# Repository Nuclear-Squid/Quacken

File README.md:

# Quacken

Libre, ergonomic, *polymorphic*: a single PCB for many possible layouts.

[3×6, 3×5, hummingbird, and everything in between](https://html-preview.github.io/?url=https%3A%2F%2Fgithub.com%2FNuclear-Squid%2FQuacken%2Fblob%2Fmain%2Findex.html).

## Roadmap

- [x] **Quacken Zero**: unibody
  - [x] first batch with a Pro Micro slot, to experiment geometry and design choices
  - [ ] next batches with an onboard nRF52840 (Bluetooth LE) and the updated geometry

- [x] **Quacken Flex**: unibody by default, splittable by choice
  - [x] onboard RP2040 (left) and I/O expander (right)
  - [x] splittable in two (I²C communication over a TRRS cable)
  - [x] splittable outer columns
  - [ ] hotswap sockets
  - [ ] optional Circle Trackpad
  - [x] optional rotary encoders

- [ ] **Marie-Quackenette**: split and wireless variant of the Quacken Flex.

## To flash the Quacken

You just need to push the little switch near the MCU, with the lightning sign, while you plug the USB cable in. Your Quacken will be detected as a storage device.
You may copy your beloved config file on this device through your file manager.
The Quacken will read the new file and reboot in normal mode, with your new config applied.

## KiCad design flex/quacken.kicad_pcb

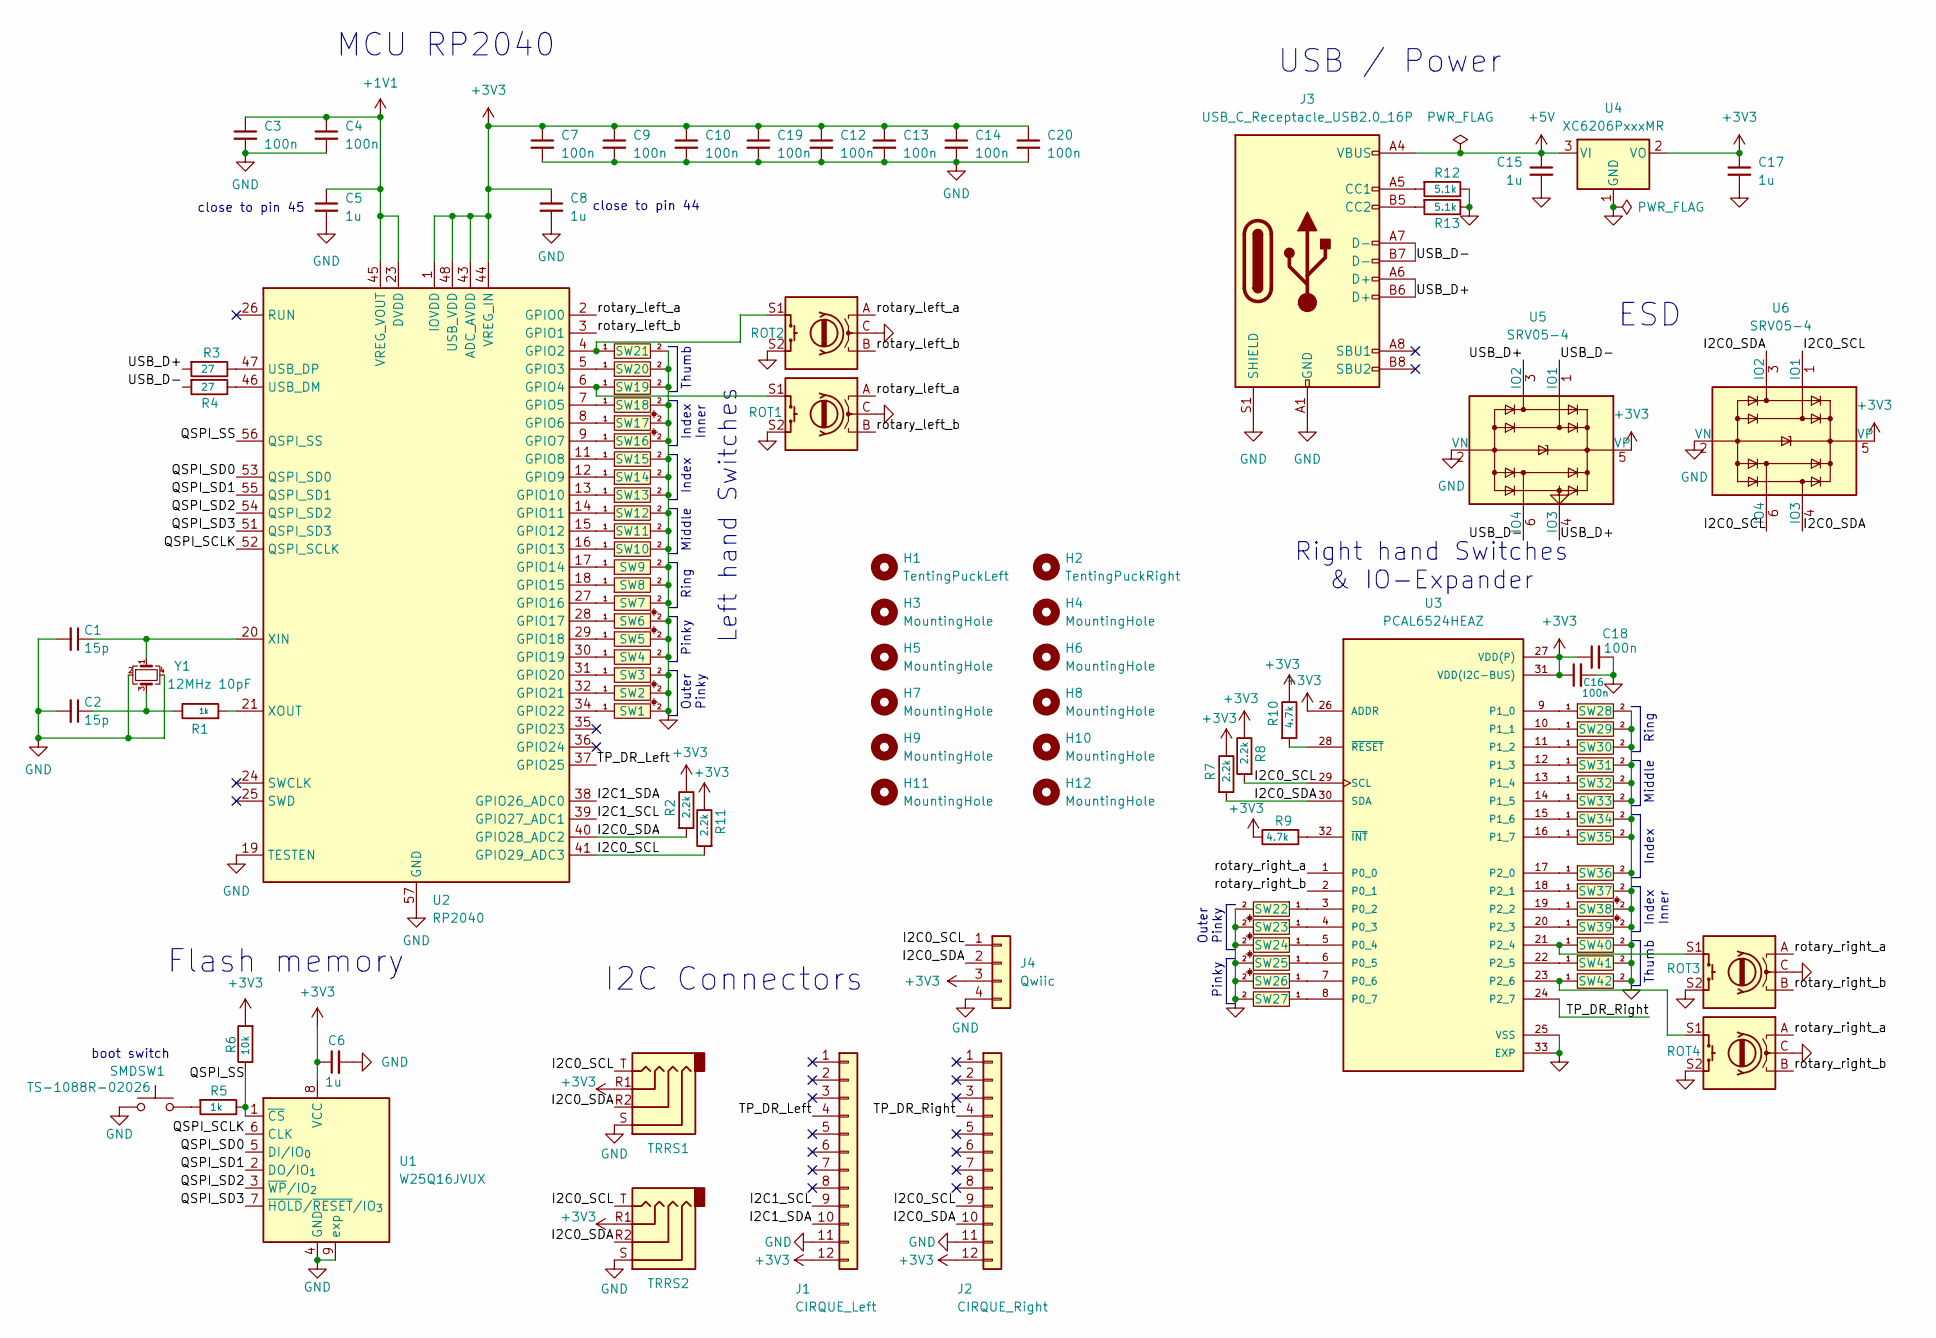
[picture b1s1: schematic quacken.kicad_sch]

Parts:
C1, C2: 15p; C_0402_1005Metric
C3, C4, C7, C9, C10, C12, C13, C14, C16, C18, C19, C20: 100n; C_0402_1005Metric
C5, C6, C8, C15, C17: 1u; C_0402_1005Metric
H1: TentingPuckLeft; TentingPuck
H2: TentingPuckRight; TentingPuck
H3, H4, H5, H6, H7, H8, H9, H10, H11, H12: MountingHole; MountingHole_2.2mm_M2_DIN965_Pad_TopOnly
J1: CIRQUE_Left; Cirque; JLCPCB Part # C2911838
J2: CIRQUE_Right; Cirque; JLCPCB Part # C2911838
J3: USB_C_Receptacle_USB2.0_16P; USB_C_Receptacle_HRO_TYPE-C-31-M-12; JLCPCB Part # C165948
J4: Qwiic; JST_SH_SM04B-SRSS-TB_1x04-1MP_P1.00mm_Horizontal
R1, R5: 1k; R_0402_1005Metric; JLCPCB Part # C11702
R2, R7, R8, R11: 2.2k; R_0402_1005Metric; JLCPCB Part # C25768
R3, R4: 27; R_0402_1005Metric
R6: 10k; R_0402_1005Metric; JLCPCB Part # C25744
R9, R10: 4.7k; R_0402_1005Metric; JLCPCB Part # C25768
R12, R13: 5.1k; R_0402_1005Metric; JLCPCB Part # C25905
ROT1, ROT2, ROT3, ROT4: RotaryEncoder_Switch; rotary_encoder
SMDSW1: TS-1088R-02026; SW_SPST_TS-1088-xR020; JLCPCB Part # C720477
SW1, SW2, SW5, SW6, SW16, SW17, SW23, SW24, SW25, SW26, SW38, SW39: Choc_Switch_Median
SW3, SW4, SW7, SW8, SW9, SW10, SW11, SW12, SW13, SW14, SW15, SW18, SW19, SW20, SW21, SW22, SW27, SW28, SW29, SW30, SW31, SW32, SW33, SW34, SW35, SW36, SW37, SW40, SW41, SW42: Choc_Switch
TRRS1, TRRS2: AudioJack4; TRRS-PJ-320A-dual; JLCPCB Part # C12569
U1: W25Q16JVUX; Winbond_USON-8-1EP_3x2mm_P0.5mm_EP0.2x1.6mm; JLCPCB Part # C2843335
U2: RP2040; QFN-56-1EP_7x7mm_P0.4mm_EP3.2x3.2mm; JLCPCB Part # C2040
U3: PCAL6524HEAZ; PCAL6524HEHZ; JLCPCB Part # C3000497
U4: XC6206PxxxMR; SOT-23-3; JLCPCB Part # C5446
U5, U6: SRV05-4; SOT-23-6; JLCPCB Part # C2836319
Y1: 12MHz 10pF; Crystal_SMD_3225-4Pin_3.2x2.5mm; MFR.Part # C20625731; JLCPCB Part # C91749

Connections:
+1V1: C3.1, C4.1, C5.1, U2.23 (DVDD), U2.45 (VREG_VOUT), U2.50 (DVDD)
+3V3: C6.1, C7.1, C8.1, C9.1, C10.1, C12.1, C13.1, C14.1, C16.1, C17.1, C18.1, C19.1, C20.1, J1.12, J2.12, J4.3, R2.1, R6.2, R7.1, R8.1, R9.1, R10.1, R11.1, TRRS1.R1, TRRS2.R1, U1.8 (VCC), U2.1 (IOVDD), U2.10 (IOVDD), U2.22 (IOVDD), U2.33 (IOVDD), U2.42 (IOVDD), U2.43 (ADC_AVDD), U2.44 (VREG_IN), U2.48 (USB_VDD), U2.49 (IOVDD), U3.26 (ADDR), U3.27 (VDD(P)), U3.31 (VDD(I2C-BUS)), U4.2 (VO), U5.5 (VP), U6.5 (VP)
+5V: C15.1, J3.A4 (VBUS), J3.A9 (VBUS), J3.B4 (VBUS), J3.B9 (VBUS), U4.3 (VI)
/I2C0_SCL: J2.9, J4.1, R8.2, R11.2, TRRS1.T, TRRS2.T, U2.41 (GPIO29_ADC3), U3.29 (SCL), U6.1 (IO1), U6.6 (IO4)
/I2C0_SDA: J2.10, J4.2, R2.2, R7.2, TRRS1.R2, TRRS2.R2, U2.40 (GPIO28_ADC2), U3.30 (SDA), U6.3 (IO2), U6.4 (IO3)
/I2C1_SCL: J1.9, U2.39 (GPIO27_ADC1)
/I2C1_SDA: J1.10, U2.38 (GPIO26_ADC0)
/QSPI_SCLK: U1.6 (CLK), U2.52 (QSPI_SCLK)
/QSPI_SD0: U1.5 (DI/IO_{0}), U2.53 (QSPI_SD0)
/QSPI_SD1: U1.2 (DO/IO_{1}), U2.55 (QSPI_SD1)
/QSPI_SD2: U1.3 (~WP/IO_{2}), U2.54 (QSPI_SD2)
/QSPI_SD3: U1.7 (~HOLD/~RESET/IO_{3}), U2.51 (QSPI_SD3)
/QSPI_SS: R5.1, R6.1, U1.1 (~CS), U2.56 (QSPI_SS)
/TP_DR_Left: J1.4, U2.37 (GPIO25)
/TP_DR_Right: J2.4, U3.24 (P2_7)
/USB_D+: J3.A6 (D+), J3.B6 (D+), R3.2, U5.3 (IO2), U5.4 (IO3)
/USB_D-: J3.A7 (D-), J3.B7 (D-), R4.2, U5.1 (IO1), U5.6 (IO4)
/rotary_left_a: ROT1.A, ROT2.A, U2.2 (GPIO0)
/rotary_left_b: ROT1.B, ROT2.B, U2.3 (GPIO1)
/rotary_right_a: ROT3.A, ROT4.A, U3.1 (P0_0)
/rotary_right_b: ROT3.B, ROT4.B, U3.2 (P0_1)
GND: C1.2, C2.2, C3.2, C4.2, C5.2, C6.2, C7.2, C8.2, C9.2, C10.2, C12.2, C13.2, C14.2, C15.2, C16.2, C17.2, C18.2, C19.2, C20.2, J1.11, J2.11, J3.A1 (GND), J3.A12 (GND), J3.B1 (GND), J3.B12 (GND), J3.S1 (SHIELD), J4.4, R12.1, R13.1, ROT1.C, ROT1.S2, ROT2.C, ROT2.S2, ROT3.C, ROT3.S2, ROT4.C, ROT4.S2, SMDSW1.1, SW1.2, SW2.2, SW3.2, SW4.2, SW5.2, SW6.2, SW7.2, SW8.2, SW9.2, SW10.2, SW11.2, SW12.2, SW13.2, SW14.2, SW15.2, SW16.2, SW17.2, SW18.2, SW19.2, SW20.2, SW21.2, SW22.2, SW23.2, SW24.2, SW25.2, SW26.2, SW27.2, SW28.2, SW29.2, SW30.2, SW31.2, SW32.2, SW33.2, SW34.2, SW35.2, SW36.2, SW37.2, SW38.2, SW39.2, SW40.2, SW41.2, SW42.2, TRRS1.S, TRRS2.S, U1.4 (GND), U1.9 (exp), U2.19 (TESTEN), U2.57 (GND), U3.25 (VSS), U3.33 (EXP), U4.1 (GND), U5.2 (VN), U6.2 (VN), Y1.2, Y1.4
unnamed: C2.1, R1.1, Y1.3
unnamed: J3.A5 (CC1), R12.2
unnamed: J3.B5 (CC2), R13.2
unnamed: R5.2, SMDSW1.2
unnamed: ROT2.S1, SW21.1, U2.4 (GPIO2)
unnamed: SW20.1, U2.5 (GPIO3)
unnamed: ROT1.S1, SW19.1, U2.6 (GPIO4)
unnamed: SW18.1, U2.7 (GPIO5)
unnamed: SW17.1, U2.8 (GPIO6)
unnamed: SW16.1, U2.9 (GPIO7)
unnamed: SW15.1, U2.11 (GPIO8)
unnamed: SW14.1, U2.12 (GPIO9)
unnamed: SW13.1, U2.13 (GPIO10)
unnamed: SW12.1, U2.14 (GPIO11)
unnamed: SW11.1, U2.15 (GPIO12)
unnamed: SW10.1, U2.16 (GPIO13)
unnamed: SW9.1, U2.17 (GPIO14)
unnamed: SW8.1, U2.18 (GPIO15)
unnamed: SW7.1, U2.27 (GPIO16)
unnamed: SW6.1, U2.28 (GPIO17)
unnamed: SW5.1, U2.29 (GPIO18)
unnamed: SW4.1, U2.30 (GPIO19)
unnamed: SW3.1, U2.31 (GPIO20)
unnamed: SW2.1, U2.32 (GPIO21)
unnamed: SW1.1, U2.34 (GPIO22)
unnamed: R4.1, U2.46 (USB_DM)
unnamed: R3.1, U2.47 (USB_DP)
unnamed: C1.1, U2.20 (XIN), Y1.1
unnamed: R1.2, U2.21 (XOUT)
unnamed: SW22.1, U3.3 (P0_2)
unnamed: SW23.1, U3.4 (P0_3)
unnamed: SW24.1, U3.5 (P0_4)
unnamed: SW25.1, U3.6 (P0_5)
unnamed: SW26.1, U3.7 (P0_6)
unnamed: SW27.1, U3.8 (P0_7)
unnamed: SW28.1, U3.9 (P1_0)
unnamed: SW29.1, U3.10 (P1_1)
unnamed: SW30.1, U3.11 (P1_2)
unnamed: SW31.1, U3.12 (P1_3)
unnamed: SW32.1, U3.13 (P1_4)
unnamed: SW33.1, U3.14 (P1_5)
unnamed: SW34.1, U3.15 (P1_6)
unnamed: SW35.1, U3.16 (P1_7)
unnamed: SW36.1, U3.17 (P2_0)
unnamed: SW37.1, U3.18 (P2_1)
unnamed: SW38.1, U3.19 (P2_2)
unnamed: SW39.1, U3.20 (P2_3)
unnamed: ROT3.S1, SW40.1, U3.21 (P2_4)
unnamed: SW41.1, U3.22 (P2_5)
unnamed: ROT4.S1, SW42.1, U3.23 (P2_6)
unnamed: R9.2, U3.32 (~INT)
unnamed: R10.2, U3.28 (~RESET)

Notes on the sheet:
close to pin 45
Flash memory
USB / Power
Middle
Index Inner
Index
Left hand Switches
MCU RP2040
Ring
Outer Pinky
I2C Connectors
close to pin 44
Thumb
Pinky
ESD
boot switch
Right hand Switches & IO-Expander

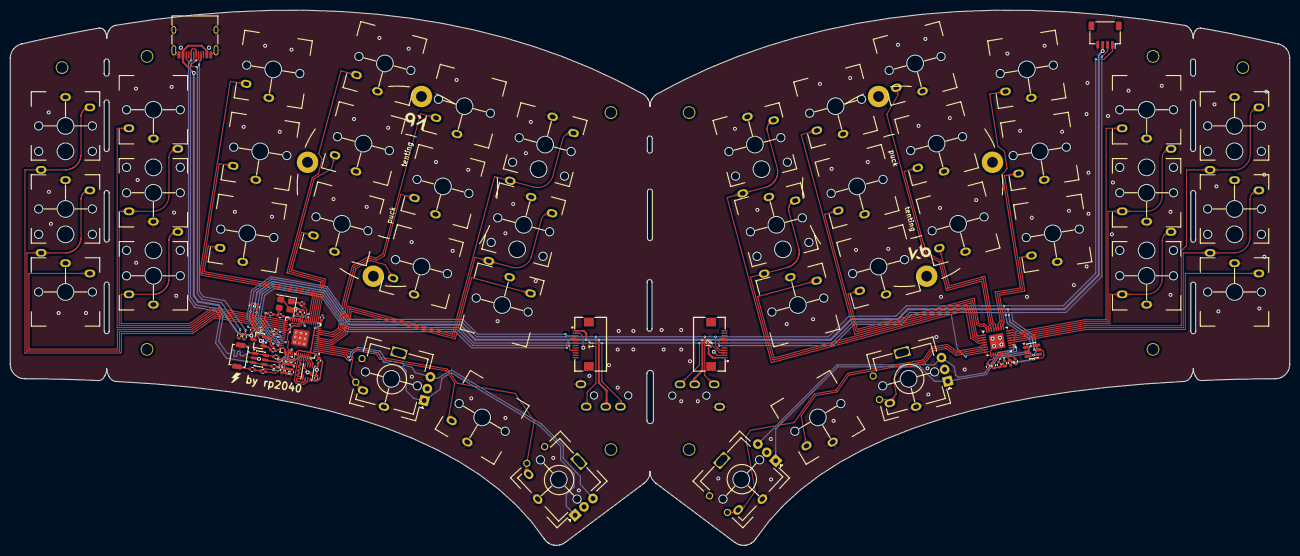
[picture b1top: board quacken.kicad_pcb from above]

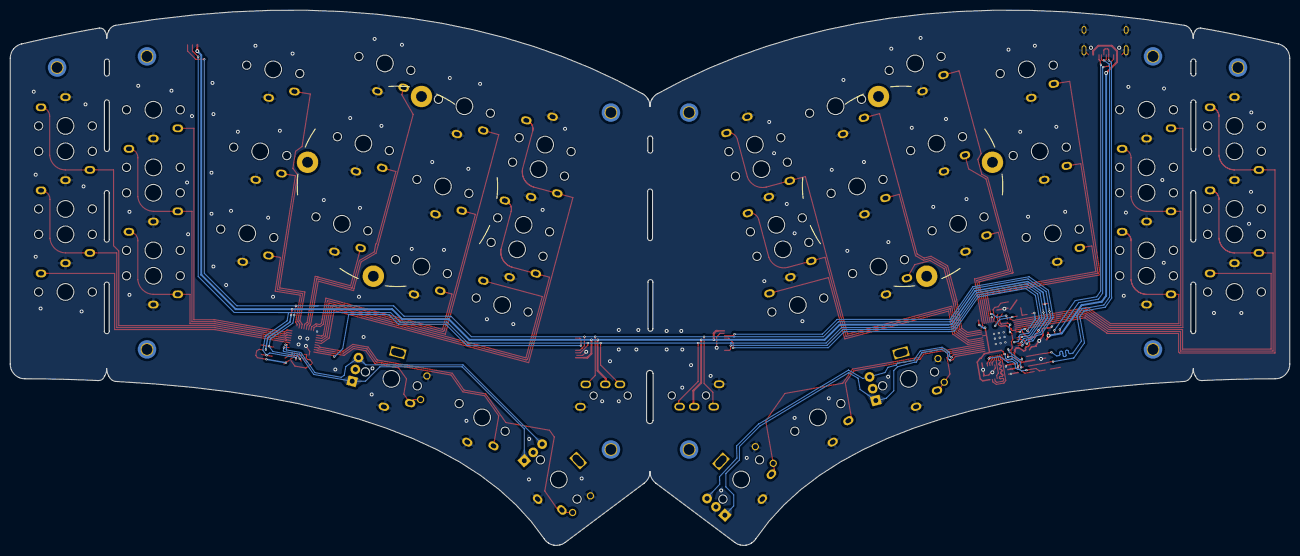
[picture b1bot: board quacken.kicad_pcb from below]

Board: 2 copper layers, 262.0 x 109.6 mm, 104 parts (10 on the bottom side), 74 nets.

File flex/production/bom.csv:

Designator,Footprint,Quantity,Value,LCSC Part #
"C1, C2",0402,2,15p,C1548
"C10, C12, C13, C14, C16, C18, C19, C20, C3, C4, C7, C9",0402,12,100n,C1525
"C15, C17, C5, C6, C8",0402,5,1u,C52923
"J1, J2",Cirque,2,"CIRQUE_Left, CIRQUE_Right",C2911838
J3,USB_C_Receptacle_HRO_TYPE-C-31-M-12,1,USB_C_Receptacle_USB2.0_16P,C165948
J4,JST_SH_SM04B-SRSS-TB_1x04-1MP_P1.00mm_Horizontal,1,Qwiic,C160404
"R1, R5",0402,2,1k,C11702
"R10, R9",0402,2,4.7k,C25900
"R11, R2, R7, R8",0402,4,2.2k,C25879
"R12, R13",0402,2,5.1k,C25905
"R3, R4",0402,2,27,C2909343
R6,0402,1,10k,C25744
"TRRS1, TRRS2",TRRS-PJ-320A-dual,2,AudioJack4,C2884926
SMDSW1,SW_SPST_TS-1088-xR020,1,TS-1088R-02026,C720477
U1,Winbond_USON-8-1EP_3x2mm_P0.5mm_EP0.2x1.6mm,1,W25Q16JVUX,C2843335
U2,QFN-56-1EP_7x7mm_P0.4mm_EP3.2x3.2mm,1,RP2040,C2040
U3,PCAL6524HEHZ,1,PCAL6524HEAZ,C3000497
U4,SOT-23-3,1,XC6206PxxxMR,C5446
"U5, U6",SOT-23-6,2,SRV05-4,C2836319
Y1,Crystal_SMD_3225-4Pin_3.2x2.5mm,1,12MHz 10pF,C91749

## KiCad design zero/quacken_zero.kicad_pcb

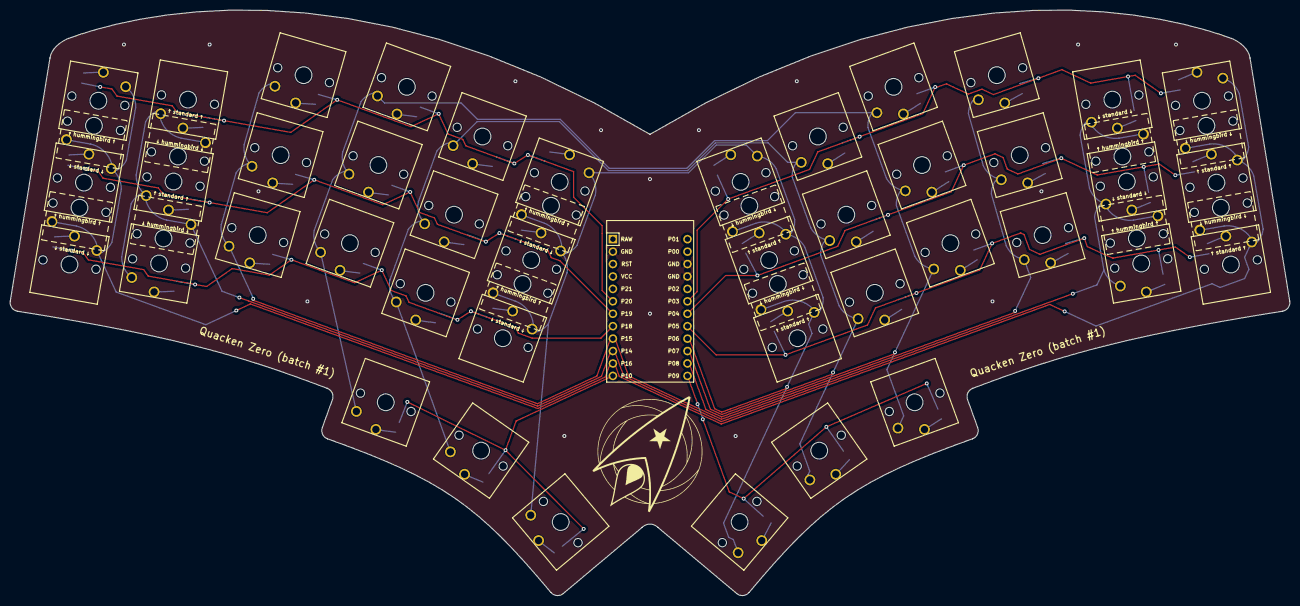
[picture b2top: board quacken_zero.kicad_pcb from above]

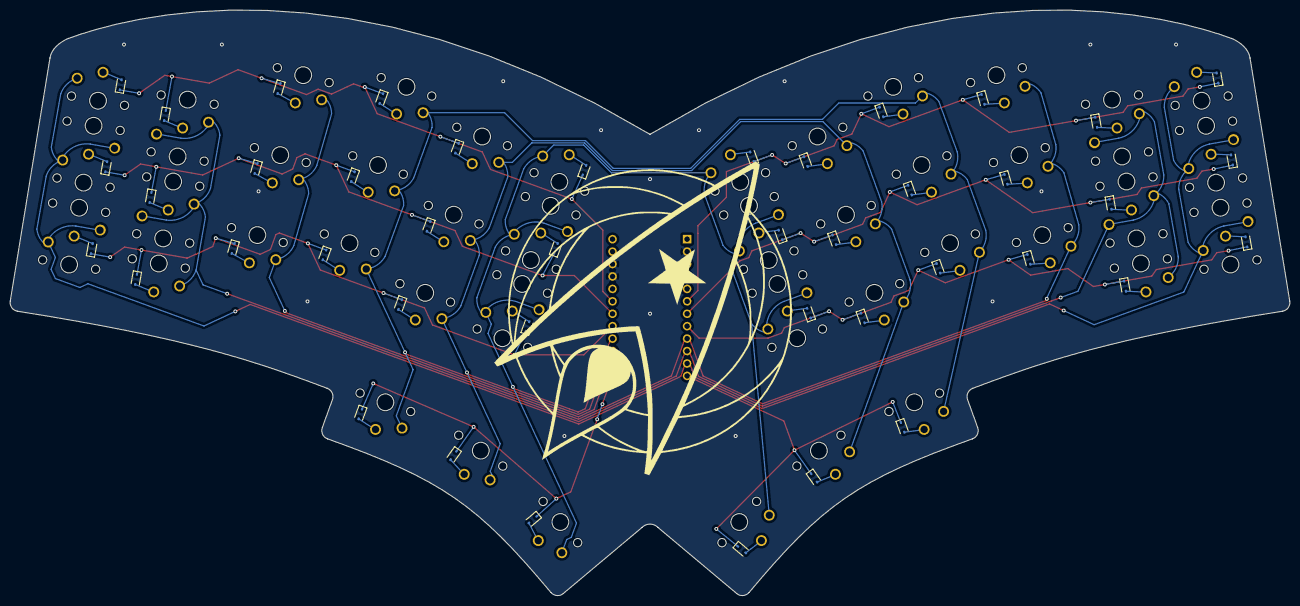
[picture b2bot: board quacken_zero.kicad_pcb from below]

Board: 2 copper layers, 261.5 x 119.6 mm, 85 parts (42 on the bottom side), 57 nets.

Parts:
D1, D2, D3, D4, D5, D6, D7, D8, D9, D10, D11, D12, D13, D14, D15, D16, D17, D18, D19, D20, D21, D22, D23, D24, D25, D26, D27, D28, D29, D30, D31, D32, D33, D34, D35, D36, D37, D38, D39, D40, D41, D42: D_SOD-323
MCU1: ProMicro
S1, S2, S3, S4, S5, S6, S7, S8, S9, S10, S11, S12, S13, S14, S15, S16, S17, S18, S19, S20, S21, S22, S23, S24, S25, S26, S27, S28, S29, S30, S31, S32, S33, S34, S35, S36, S37, S38, S39, S40, S41, S42: PG1350

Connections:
GND: MCU1.2, MCU1.15, MCU1.16
P3: D18.1, D21.1, D24.1, D27.1, D39.1, D42.1, MCU1.18
P4: D17.1, D20.1, D23.1, D26.1, D38.1, D41.1, MCU1.19
P5: D16.1, D19.1, D22.1, D25.1, D37.1, D40.1, MCU1.20
P6: MCU1.21, S15.1, S30.1, S34.1, S34.3, S35.1, S35.3, S36.1, S40.1, S40.3, S41.1, S41.3, S42.1
P7: MCU1.22, S10.1, S11.1, S12.1, S14.1, S25.1, S26.1, S27.1, S29.1
P8: MCU1.23, S7.1, S8.1, S9.1, S13.1, S22.1, S23.1, S24.1, S28.1
P9: D28.1, D29.1, D30.1, MCU1.24
P10: D13.1, D14.1, D15.1, MCU1.12
P14: MCU1.10, S1.1, S2.1, S2.3, S3.1, S3.3, S16.1, S17.1, S17.3, S18.1, S18.3
P15: MCU1.9, S4.1, S5.1, S6.1, S19.1, S20.1, S21.1
P16: MCU1.11, S31.1, S31.3, S32.1, S32.3, S33.1, S37.1, S37.3, S38.1, S38.3, S39.1
P18: D1.1, D4.1, D7.1, D10.1, D31.1, D34.1, MCU1.8
P19: D2.1, D5.1, D8.1, D11.1, D32.1, D35.1, MCU1.7
P20: D3.1, D6.1, D9.1, D12.1, D33.1, D36.1, MCU1.6
comfy_default: D14.2, S14.2
index_bottom: D10.2, S10.2
index_home: D11.2, S11.2
index_top: D12.2, S12.2
inner_bottom: D34.2, S34.2
inner_home: D35.2, S35.2
inner_top: D36.2, S36.2
middle_bottom: D7.2, S7.2
middle_home: D8.2, S8.2
middle_top: D9.2, S9.2
mirror_comfy_default: D29.2, S29.2
mirror_index_bottom: D25.2, S25.2
mirror_index_home: D26.2, S26.2
mirror_index_top: D27.2, S27.2
mirror_inner_bottom: D40.2, S40.2
mirror_inner_home: D41.2, S41.2
mirror_inner_top: D42.2, S42.2
mirror_middle_bottom: D22.2, S22.2
mirror_middle_home: D23.2, S23.2
mirror_middle_top: D24.2, S24.2
mirror_outer_bottom: D37.2, S37.2
mirror_outer_home: D38.2, S38.2
mirror_outer_top: D39.2, S39.2
mirror_pinky_bottom: D16.2, S16.2
mirror_pinky_home: D17.2, S17.2
mirror_pinky_top: D18.2, S18.2
mirror_reachy_default: D30.2, S30.2
mirror_ring_bottom: D19.2, S19.2
mirror_ring_home: D20.2, S20.2
mirror_ring_top: D21.2, S21.2
mirror_tucky_default: D28.2, S28.2
outer_bottom: D31.2, S31.2
outer_home: D32.2, S32.2
outer_top: D33.2, S33.2
pinky_bottom: D1.2, S1.2
pinky_home: D2.2, S2.2
pinky_top: D3.2, S3.2
reachy_default: D15.2, S15.2
ring_bottom: D4.2, S4.2
ring_home: D5.2, S5.2
ring_top: D6.2, S6.2
tucky_default: D13.2, S13.2

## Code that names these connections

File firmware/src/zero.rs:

/**
The Quacken Zero physical matrix misses Keyberon's expectations on 2 points:
 - it doesn't match the logical layout
 - it is set col2row with pull-down inputs

Besides, the ProMicro GPIO pinout used by Ergogen and ZMK rely on the ProMicro Atmel IDs
-- but rb2040_hal, obviously, does not. So we need a Matrix factory for every ProMicro controller.

    .   +----USB----+               +----USB----+            D+ +----USB----+ D-
    . 1 |           | RAW         0 |           | RAW         1 |           | RAW
    . 0 |           | GND         1 |           | GND         0 |           | GND
    GND | SparkFun  | RST       GND | SparkFun  | RST       GND | Adafruit  | RST
    GND |   Atmel   | VCC       GND |  rp2040   | VCC       GND |  kb2040   | VCC
    . 2 |           | 21          2 |           | 29          2 |           | 29
    . 3 |           | 20          3 |           | 28          3 |           | 28
    . 4 |           | 19          4 |           | 27          4 |           | 27
    . 5 |           | 18          5 |           | 26          5 |           | 26
    . 6 |           | 15          6 |           | 22          6 |           | 18
    . 7 |           | 14          7 |           | 20          7 |           | 20
    . 8 |           | 16          8 |           | 23          8 |           | 19
    . 9 |___________| 10          9 |___________| 21          9 |___________| 10
**/
// The logical layout is a 12×4 matrix: 3×6 + 3 thumb keys for each hand.
// Ergogen has generated an 8*6 matrix rather than a 12×4 one, in order to save two pins:
// the two halves are stacked onto one anather. So here’s q quick helper to work around that.
use crate::layout;
const MATRIX_COLS: usize = 6;
const MATRIX_ROWS: usize = 8;

// this could be done with keyberon's debouncer (`transform` function)
fn matrix_to_layout(row: usize, col: usize) -> (usize, usize) {
    if row >= layout::ROWS {
        (row - layout::ROWS, layout::COLS - col - 1)
    } else {
        (row, col)
    }
}

// Keyberon expects rows to bo outputs, and columns to be pull-up inputs. ("row2col" on ZMK)
// On the Quacken Zero, rows are pull-down inputs and columns are outputs. ("col2row" on ZMK)
// So here's a `Col2RowMatrix` type to implement this.

// rp2040 implementations of the embedded_hal::digital::InputPin,OutputPin} traits
use embedded_hal::digital::{InputPin, OutputPin};
use rp2040_hal::gpio;
type KbInputPin = gpio::Pin<gpio::DynPinId, gpio::FunctionSioInput, gpio::PullDown>;
type KbOutputPin = gpio::Pin<gpio::DynPinId, gpio::FunctionSioOutput, gpio::PullDown>;

pub type QuackenZeroMatrix = Col2RowMatrix<KbOutputPin, KbInputPin>;

use core::convert::Infallible;

pub struct Col2RowMatrix<C, R>
where
    C: OutputPin,
    R: InputPin,
{
    cols: [C; MATRIX_COLS],
    rows: [R; MATRIX_ROWS],
}

impl<C, R> Col2RowMatrix<C, R>
where
    C: OutputPin,
    R: InputPin,
{
    /// Creates a new Matrix.
    ///
    /// Assumes rows are pull-down inputs, and columns are output pins
    /// which are set low when not being scanned.
    pub fn new<E>(cols: [C; MATRIX_COLS], rows: [R; MATRIX_ROWS]) -> Result<Self, E>
    where
        C: OutputPin<Error = E>,
        R: InputPin<Error = E>,
    {
        let mut res = Self { cols, rows };
        res.clear()?;
        Ok(res)
    }

    /// Clears the matrix.
    fn clear<E>(&mut self) -> Result<(), E>
    where
        C: OutputPin<Error = E>,
        R: InputPin<Error = E>,
    {
        for c in self.cols.iter_mut() {
            c.set_low()?;
        }
        Ok(())
    }

    /// Creates a new Generic ProMicro matrix.
    pub fn new_promicro(pins: gpio::Pins) -> Result<QuackenZeroMatrix, Infallible> {
        QuackenZeroMatrix::new(
            [
                pins.gpio8.into_push_pull_output().into_dyn_pin(),
                pins.gpio7.into_push_pull_output().into_dyn_pin(),
                pins.gpio6.into_push_pull_output().into_dyn_pin(),
                pins.gpio16.into_push_pull_output().into_dyn_pin(),
                pins.gpio14.into_push_pull_output().into_dyn_pin(),
                pins.gpio15.into_push_pull_output().into_dyn_pin(),
            ],
            [
                pins.gpio3.into_pull_down_input().into_dyn_pin(),
                pins.gpio4.into_pull_down_input().into_dyn_pin(),
                pins.gpio5.into_pull_down_input().into_dyn_pin(),
                pins.gpio9.into_pull_down_input().into_dyn_pin(),
                pins.gpio20.into_pull_down_input().into_dyn_pin(),
                pins.gpio19.into_pull_down_input().into_dyn_pin(),
                pins.gpio18.into_pull_down_input().into_dyn_pin(),
                pins.gpio10.into_pull_down_input().into_dyn_pin(),
            ],
        )
    }

    /// Creates a new SparkFun ProMicro RP2040 matrix.
    pub fn new_sparkfun_rp2040(pins: gpio::Pins) -> Result<QuackenZeroMatrix, Infallible> {
        QuackenZeroMatrix::new(
            [
                pins.gpio8.into_push_pull_output().into_dyn_pin(),
                pins.gpio7.into_push_pull_output().into_dyn_pin(),
                pins.gpio6.into_push_pull_output().into_dyn_pin(),
                pins.gpio23.into_push_pull_output().into_dyn_pin(), // promicro 16
                pins.gpio20.into_push_pull_output().into_dyn_pin(), // promicro 14
                pins.gpio22.into_push_pull_output().into_dyn_pin(), // promicro 15
            ],
            [
                pins.gpio3.into_pull_down_input().into_dyn_pin(),
                pins.gpio4.into_pull_down_input().into_dyn_pin(),
                pins.gpio5.into_pull_down_input().into_dyn_pin(),
                pins.gpio9.into_pull_down_input().into_dyn_pin(),
                pins.gpio28.into_pull_down_input().into_dyn_pin(), // promicro 20
                pins.gpio27.into_pull_down_input().into_dyn_pin(), // promicro 19
                pins.gpio26.into_pull_down_input().into_dyn_pin(), // promicro 18
                pins.gpio21.into_pull_down_input().into_dyn_pin(), // promicro 10
            ],
        )
    }

    // To use after creating the QuackenZeroMatrix if the microcontroller was soldered face down.
    // Cols and rows order is modified like this:
    // [c0, c1, c2, c3, c4, c5]           --> [c3, c4, c5, c0, c1, c2]
    // [r0, r1, r2, r3, r4, r5, r6, r7]   --> [r4, r5, r6, r7, r0, r1, r2, r3]
    pub fn upside_down(&mut self) {
        self.cols.rotate_left(MATRIX_COLS / 2);
        self.rows.rotate_left(MATRIX_ROWS / 2);
    }

    /// Scans the matrix and checks which keys are pressed.
    ///
    /// Every column pin in order is pulled high, and then each row pin is tested:
    /// if it's high, the key is marked as pressed.
    ///
    /// Delay function allows pause to let input pins settle.
    pub fn get_with_delay<F: FnMut(), E>(
        &mut self,
        mut delay: F,
    ) -> Result<[[bool; layout::COLS]; layout::ROWS], E>
    where
        C: OutputPin<Error = E>,
        R: InputPin<Error = E>,
    {
        let mut keys = [[false; layout::COLS]; layout::ROWS];

        for (ci, col) in self.cols.iter_mut().enumerate() {
            col.set_high()?;
            delay();
            for (ri, row) in self.rows.iter_mut().enumerate() {
                if row.is_high()? {
                    let (layout_row, layout_col) = matrix_to_layout(ri, ci);
                    keys[layout_row][layout_col] = true;
                }
            }
            col.set_low()?;
        }
        Ok(keys)
    }

    /// Scans the matrix and checks which keys are pressed.
    ///
    /// Every column pin in order is pulled high, and then each row pin is tested:
    /// if it's high, the key is marked as pressed.
    pub fn get<E>(&mut self) -> Result<[[bool; layout::COLS]; layout::ROWS], E>
    where
        C: OutputPin<Error = E>,
        R: InputPin<Error = E>,
    {
        self.get_with_delay(|| ())
    }
}

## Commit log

2025-07-23 First draft of zmk firmware
2025-07-23 Override default path to zmk config.
2025-07-23 Tried forking the upstream gh workflow build script.
2025-07-23 Fix path to zmk directory, attempt #1
2025-07-23 Fix path to zmk directory, attempt #2
2025-07-23 Fix path to zmk directory, attempt #3
2025-07-23 Fix path to zmk directory, attempt #4
2025-07-23 Fix `zephyr-export command`, attempt #1
2025-07-23 More generic fix to west related problems, attempt #1 (this is fun)
2025-07-23 More generic fix to west related problems, attempt #2
2025-07-23 More generic fix to west related problems, attempt #3 (I feel so fucking stupid)
2025-07-23 More generic fix to west related problems, attempt #4
2025-07-23 Holy shit this time it’s not the GH action’s fault?
2025-07-23 Where the fuck is my keyboard config ??
2025-07-23 Wait, maybe it *was* the gh action script actually ?
2025-07-23 So if I understand the docs, I have to rename this folder ?
2025-07-23 Forgot to change something
2025-07-23 Renaming the folder did *NOT* held. Symlink the keymap ?
2025-07-29 (wip) keyberon firmware
2025-07-29 credentials
2025-07-29 Updated `.gitignore` file.
2025-07-30 Fixed compilation errors related to usb.
2025-07-31 wip: switch to the latest rp2040_hal API
2025-07-31 12*4 => 8*6 grid
2025-07-31 low-hanging fruits (warnings)
2025-07-31 proper type casting for gpio pins
2025-07-31 proper build target
2025-07-31 basic keyboard layout
2025-08-01 Fixed linking error: necessary features on crate `rp2040-hal`.
2025-08-01 Fixed firmware upload script.
2025-08-01 RP2040 chip is now recognised as a USB peripheral.
2025-08-01 Cleanup
2025-08-01 Usb stuck in `Suspend` mode, pls help.
2025-08-01 Firmware very close to Keymini’s but no key presses ar ever detected.
2025-08-08 comment nitpicks
2025-08-08 Wip (matrix).
2025-08-08 add a QuackenZero-specific matrix
2025-08-08 transpose the Keyberon matrix
2025-08-08 fixes: proper pin refs + 1 microsecond delay
2025-08-09 proper configuration
2025-08-10 drop unused rp2040-hal features
2025-08-12 nitpick
2025-08-12 oops, forgot the README
2025-08-12 Swapped `cortex-m-rtic` for `rtic`, due to sub-dependencies issues.
    `cortex-m-rtic` depends on `heapless-0.7.7`, which in turn depends
    on `atomic-polyfill-1.0.0`, a deprecated crate that just **doesn’t**
    compile on my machine, and shouldn’t even be used in the first place.
    Swappinging it out for `rtic` solves this issue without affecting
    how the keyboard’s work at run-time.
2025-08-12 oops
2025-08-12 a bit of doc
2025-08-12 Switching to 2024 (stable).
    The recent switch to rtic[thumbv6] broke the build on my box.
    Upgrading to edition2024 and the latest stable Cargo seems to fix it.
2025-11-20 Flex 25.10
    Cleaner hierarchy
    Moved ergogen stuff to it’s own folder
    Even simpler hierarchy
    Moved production folder
2026-04-01 geometry update
2026-04-01 geometry update (#7)
2026-04-02 quick description
2026-04-02 quick description (#8)
2026-04-21 Flex: FreeCAD design file
2026-05-03 flex 25.11
2026-05-03 flex 25.11 (#11)
2026-05-03 flex 25.12
2026-05-06 flex 25.12 (#12)
2026-05-06 flex 26.01
    Removed LTC4311
    Remove silkscreen and update production files
2026-05-06 flex 26.01 (#15)
2026-05-07 Fix PCB outline
2026-05-07 Update 3D models to use .step files instead of .stpZ
    According to https://kicad.github.io/packages3d/ models are
    available in https://gitlab.com/kicad/libraries/kicad-packages3D
    and all the files are in .step format
2026-05-07 Set 3D model for the USB-C plug with similar GCT model
2026-05-07 Set 3D model UQFN-32_5x5mm_P0.5mm.step for I/O Expander
    model is 5x5x0.56mm, like in the IC specs:
    https://docs.nxp.com/bundle/PCAL6524/page/topics/package_outline.html
2026-05-07 Add custom 3D model for cirque connectors
2026-05-08 Fix PCB outline (#16)
2026-05-08 Add TRRS 3d model
2026-05-08 Update TRRS footprints from keyboard library
2026-05-22 Fix PCB reference and add sketches with measures from KiCad
2026-05-28 Rework cutholes and parametric plate for various configurations
2026-06-02 Add cutouts for button, plugs and chips Allow various plate thicknesses Allow freeing switches from top and/or bottom for thick plates
2026-06-03 Add extra hole for cirque
